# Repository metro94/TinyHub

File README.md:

# TinyHub - 4-Port USB Hub with Multi-TT

## Introduction

A tiny USB hub with support of Multi-TT (Transaction Translator), powered by CH334R.

## 3D Rendering View

## License

[CERN-OHL-P](LICENSE)

## EDA

KiCad 6.0.6

## Usages

This PCB can be used with CH334R.

`Fuse/1N4004` selection is depended on CH334 version:

* For the first version of CH334 with 0 in the penultimate 5 digits of the lot number, this device is changed to 1N4001 or similar diode.
* Otherwise, this device should be a 100mA fuse resistor, or for simplified applications, 0Ω can be used.

NOTE: For the first version of CH334R, it could be lack of Multi-TT support, and tools such as USBTreeView would report that hub is Single-TT. For my test, CH334R with the lot number `31160HC16` is **NOT** Multi-TT supported, and `31161HC43` is. I suggest to contact Qinheng for more information.

### Schematics

[TinyHub Schematic](schematics/TinyHub.pdf)

### BOM

[TinyHub BOM](https://metro94.github.io/TinyHub/bom.html)

### Product Page

[USB HUB Controller – CH334/5 - NanjingQinhengMicroelectronics](http://www.wch-ic.com/products/CH334.html)

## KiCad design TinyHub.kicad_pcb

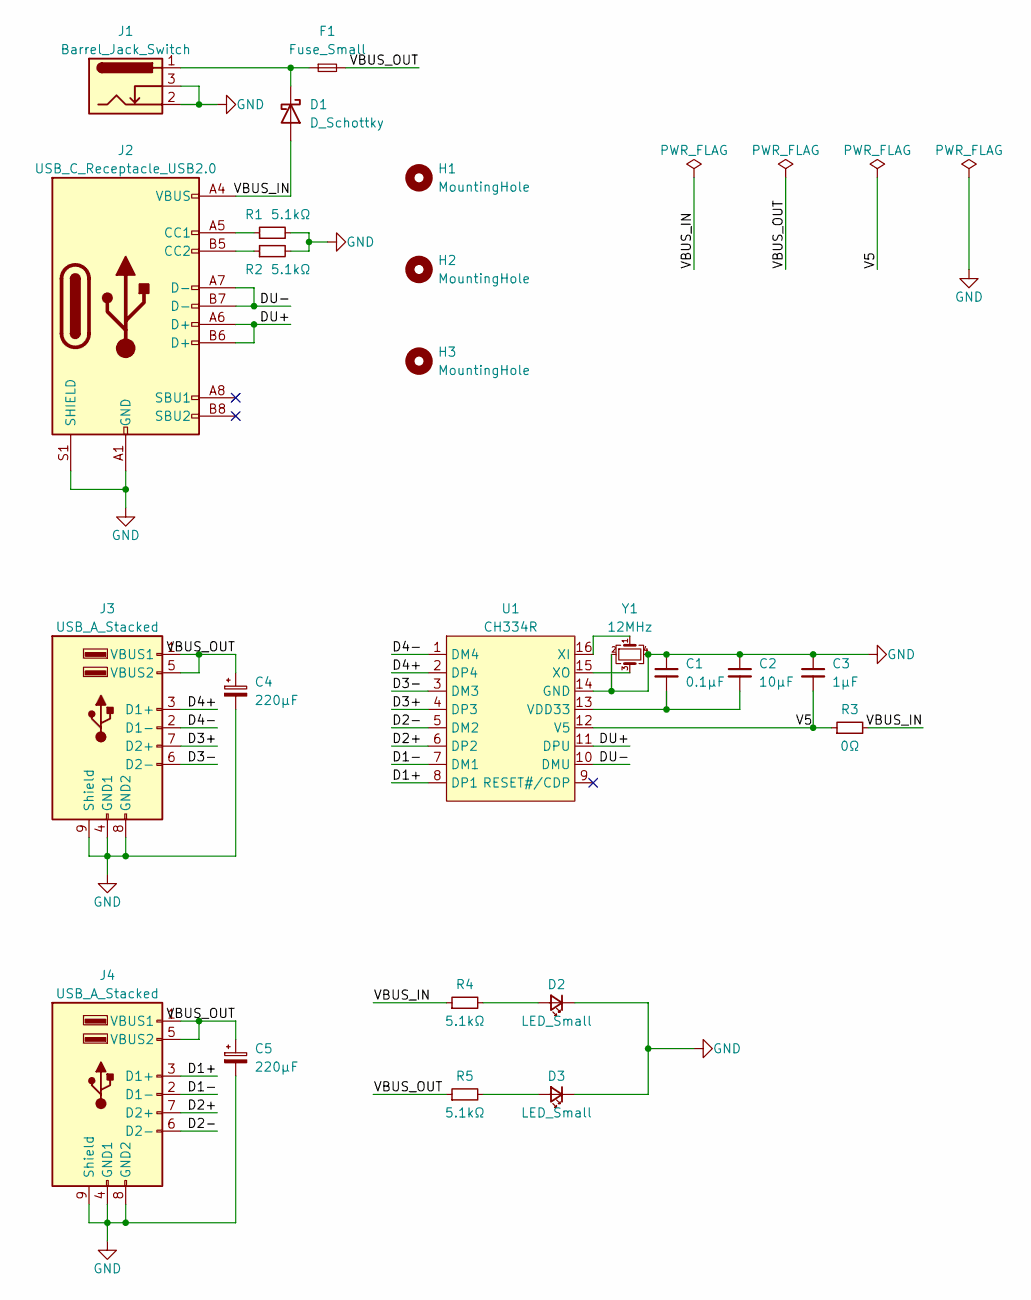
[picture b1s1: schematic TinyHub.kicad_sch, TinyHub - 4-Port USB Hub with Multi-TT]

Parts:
C1: 0.1μF; C_0603_1608Metric
C2: 10μF; C_0603_1608Metric
C3: 1μF; C_0603_1608Metric
C4, C5: 220μF; CP_Radial_D6.3mm_P2.50mm
D1: D_Schottky; D_SMA
D2, D3: LED_Small; LED_0805_2012Metric
F1: Fuse_Small; Fuse_1812_4532Metric
H1, H2, H3: MountingHole; MountingHole_2.2mm_M2
J1: Barrel_Jack_Switch; BarrelJack_Horizontal
J2: USB_C_Receptacle_USB2.0; USB_C_Receptacle_Palconn_UTC16-G
J3, J4: USB_A_Stacked; USB_Offset_Stacked
R1, R2, R4, R5: 5.1kΩ; R_0603_1608Metric
R3: 0Ω; R_0603_1608Metric
U1: CH334R; QSOP-16_3.9x4.9mm_P0.635mm
Y1: 12MHz; Crystal_SMD_3225-4Pin_3.2x2.5mm

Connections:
/D1+: J4.3 (D1+), U1.8 (DP1)
/D1-: J4.2 (D1-), U1.7 (DM1)
/D2+: J4.7 (D2+), U1.6 (DP2)
/D2-: J4.6 (D2-), U1.5 (DM2)
/D3+: J3.7 (D2+), U1.4 (DP3)
/D3-: J3.6 (D2-), U1.3 (DM3)
/D4+: J3.3 (D1+), U1.2 (DP4)
/D4-: J3.2 (D1-), U1.1 (DM4)
/DU+: J2.A6 (D+), J2.B6 (D+), U1.11 (DPU)
/DU-: J2.A7 (D-), J2.B7 (D-), U1.10 (DMU)
/V5: C3.2, R3.1, U1.12 (V5)
/VBUS_IN: D1.2 (A), J2.A4 (VBUS), J2.A9 (VBUS), J2.B4 (VBUS), J2.B9 (VBUS), R3.2, R4.1
/VBUS_OUT: C4.1, C5.1, F1.2, J3.1 (VBUS1), J3.5 (VBUS2), J4.1 (VBUS1), J4.5 (VBUS2), R5.1
GND: C1.1, C2.1, C3.1, C4.2, C5.2, D2.1 (K), D3.1 (K), J1.2, J1.3, J2.A1 (GND), J2.A12 (GND), J2.B1 (GND), J2.B12 (GND), J2.S1 (SHIELD), J3.4 (GND1), J3.8 (GND2), J3.9 (Shield), J4.4 (GND1), J4.8 (GND2), J4.9 (Shield), R1.2, R2.2, U1.14 (GND), Y1.2, Y1.4
unnamed: C1.2, C2.2, U1.13 (VDD33)
unnamed: D1.1 (K), F1.1, J1.1
unnamed: D2.2 (A), R4.2
unnamed: D3.2 (A), R5.2
unnamed: J2.A5 (CC1), R1.1
unnamed: J2.B5 (CC2), R2.1
unnamed: U1.15 (XO), Y1.3
unnamed: U1.16 (XI), Y1.1

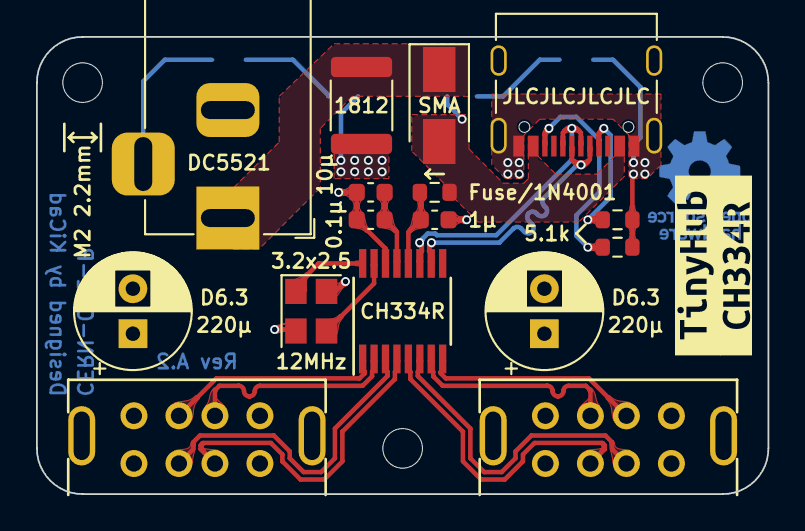
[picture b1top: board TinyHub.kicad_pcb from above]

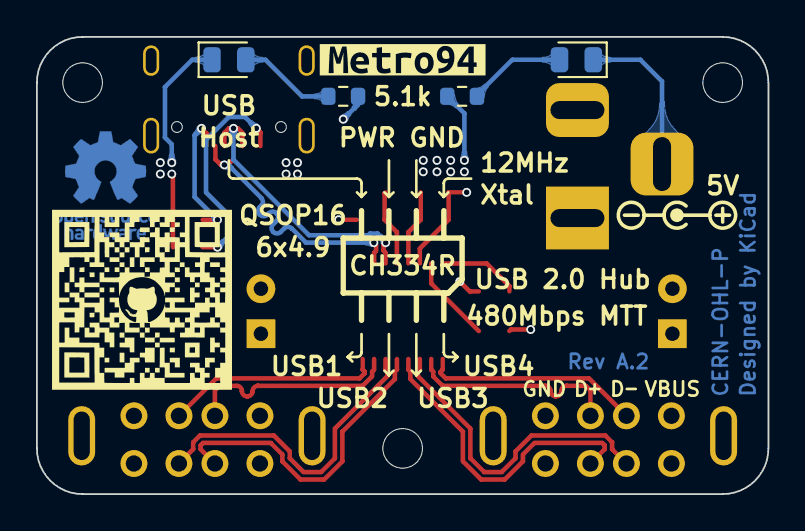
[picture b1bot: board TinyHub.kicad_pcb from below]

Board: 4 copper layers, 40.6 x 25.4 mm, 26 parts (5 on the bottom side), 22 nets.

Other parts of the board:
kibuzzard-635414B2: G***; kibuzzard-635414B2
kibuzzard-635414BB: G***; kibuzzard-635414BB
kibuzzard-63727825: G***; kibuzzard-63727825

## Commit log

2022-11-30 Rev A.2 released
